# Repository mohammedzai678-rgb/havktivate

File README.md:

# Jeevan Voice Agent

A predictive voice companion for the **VitaWatch ESP32 hardware** (MAX30102 pulse/SpO₂, MAX30205 body
temperature, OLED; the scan flow uses MAX30102 and MAX30205 only). It learns the wearer's normal, forecasts what is coming, and **speaks first**
through a Bluetooth headset (ElevenLabs voice, Gemini wording) — e.g. *"Your heartbeat seems a little fast.
Are you feeling nervous?"* — then listens for the answer, guides breathing, and (only after a clear "yes")
prepares a caregiver message.

```
msrus/
├─ firmware/jeevancare_esp32/   ESP32 C/C++ firmware — identical to VitaWatch (same pins, same Wi‑Fi, same endpoint)
├─ server/                      Python (FastAPI): ESP32 link + ElevenLabs TTS + Gemini dialogue
└─ web/                         Vite + React + TypeScript: the single Voice Agent page
```

## Hardware (unchanged)
Same board, wiring and Wi‑Fi as before — see `firmware/jeevancare_esp32/config.h`.
The ESP32 sends live readings and receives scan commands directly from the laptop over Wi-Fi. Set LOCAL_BACKEND_BASE_URL in config.h to the laptop's current Wi-Fi IPv4 address. Keep the laptop and ESP32 on the same network; the server must be reachable on port 8001.

## Run it

**1. Server** (Python 3.10+)
```powershell
cd server
python -m venv .venv
.\.venv\Scripts\pip install -r requirements.txt
copy .env.example .env        # then fill in ELEVENLABS_API_KEY and GEMINI_API_KEY
.\.venv\Scripts\python -m uvicorn main:app --host 0.0.0.0 --port 8001 --reload
```
Optional: configure the Supabase URL and service-role key in server/.env to sync telemetry and saved readings to the cloud. Sensor selection and reading history use the local service and remain available when Supabase is temporarily unreachable; offline readings are stored in server/data/scan_readings.json.

**2. Web**
```powershell
cd web
npm install
npm run dev                   # http://localhost:5173
```

**3. Headset**: pair the Bluetooth headset in Windows and set it as the default **input and output**,
open the page in Chrome, press **Start Voice Agent** (this unlocks audio so the agent may speak first).

## How the prediction works (all on the laptop, nothing learned in the cloud)
- **Learned pattern** – a personal baseline per vital (saved in the browser), updated only from non‑abnormal readings.
- **Time‑to‑event** – 60 s linear trend → "reaches attention level in ~N s (confidence %)".
- **Risk score** – 0–100 that climbs as precursors build, with a +60 s projection.
- **Speak first** – when the forecast/learned drift says something is coming, the agent opens the conversation, says *why*, then listens.
- **Adapts** – "I'm fine" makes it ask a little less about that topic next time; "not well" makes it ask sooner.

Complete HR/SpO2/temperature scans are saved to Supabase vitawatch_readings when server credentials are configured, or to server/data/scan_readings.json otherwise. Raw ESP32 samples continue to be logged to server/data/vitals_log.csv.

*Assistive early‑warning only — not a medical device, no diagnosis.*

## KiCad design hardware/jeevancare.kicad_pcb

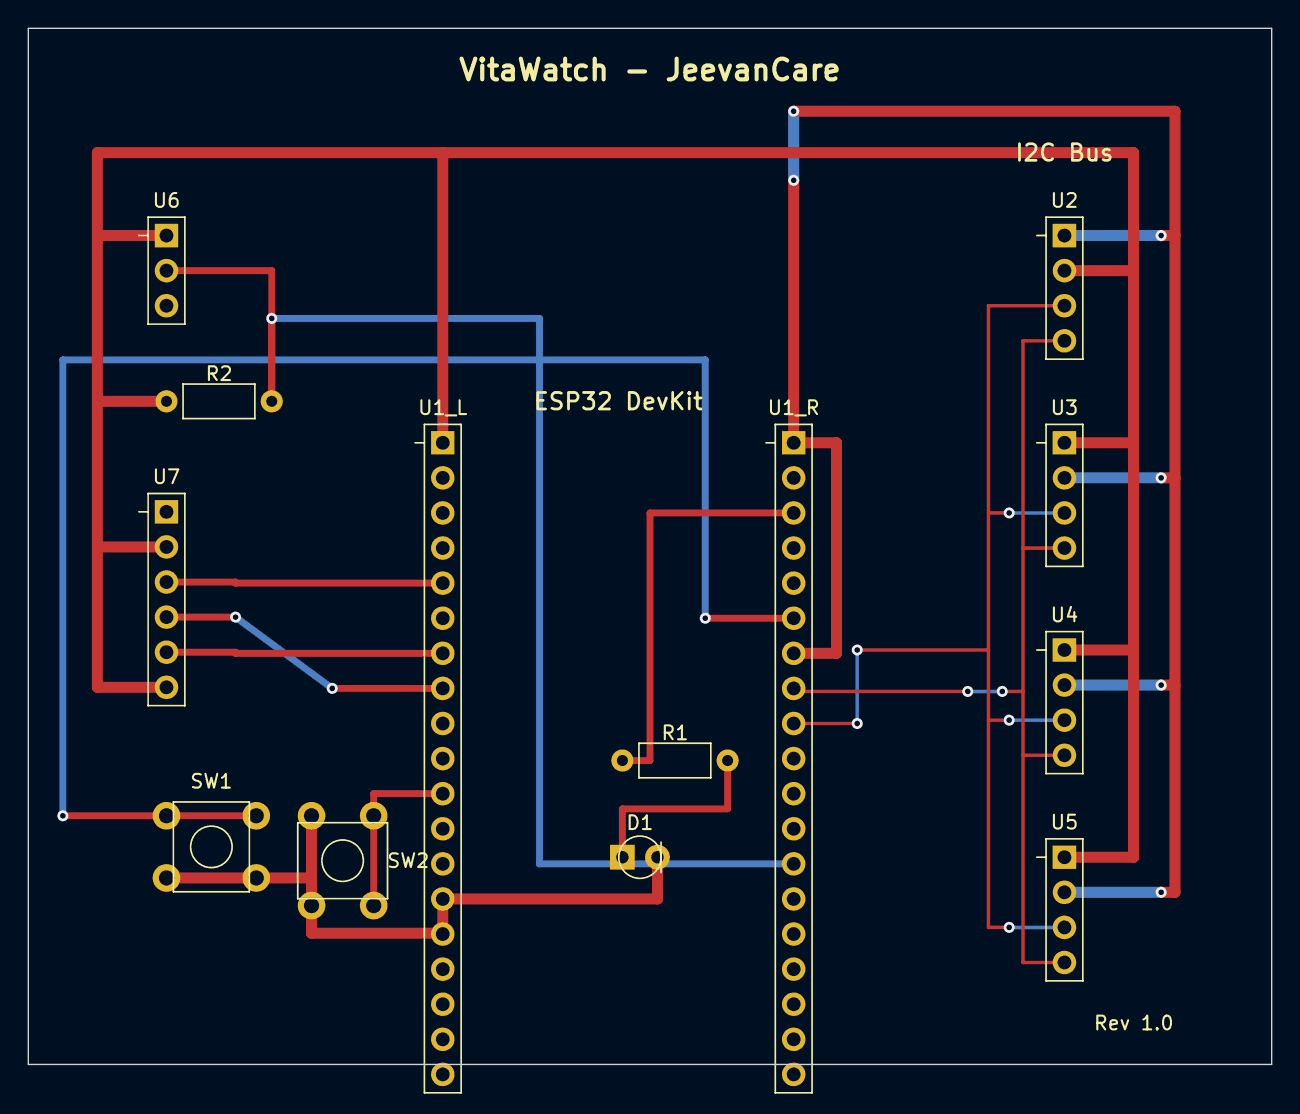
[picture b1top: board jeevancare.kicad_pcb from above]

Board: 2 copper layers, 90.0 x 75.0 mm, 13 parts (0 on the bottom side), 12 nets.

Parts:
D1: LED_Medicine; LED_D3.0mm
R1: 220R; R_Axial_DIN0207_L6.3mm_D2.5mm_P7.62mm_Horizontal
R2: 4.7k; R_Axial_DIN0207_L6.3mm_D2.5mm_P7.62mm_Horizontal
SW1: Medicine_ACK; SW_PUSH_6mm
SW2: Screen_Button; SW_PUSH_6mm
U1_L: ESP32_DevKit_Left; PinHeader_1x19_P2.54mm_Vertical
U1_R: ESP32_DevKit_Right; PinHeader_1x19_P2.54mm_Vertical
U2: SSD1306_OLED; PinHeader_1x04_P2.54mm_Vertical
U3: MAX30102; PinHeader_1x04_P2.54mm_Vertical
U4: MAX30205; PinHeader_1x04_P2.54mm_Vertical
U5: DS3231_RTC; PinHeader_1x04_P2.54mm_Vertical
U6: DHT11; PinHeader_1x03_P2.54mm_Vertical
U7: AD8232_ECG; PinHeader_1x06_P2.54mm_Vertical

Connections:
+3V3: R2.1, U1_L.1, U2.2, U3.1, U4.1, U5.1, U6.1, U7.2, U7.6
GND: D1.2, SW1.2, SW2.2, U1_L.14, U1_R.1, U1_R.7, U2.1, U3.2, U4.2, U5.2, U6.3, U7.1
GPIO4: R2.2, U1_R.13, U6.2
GPIO21: SW1.1, U1_R.6
GPIO22: R1.1, U1_R.3
GPIO27: SW2.1, U1_L.11
GPIO32: U1_L.7, U7.5
GPIO33: U1_L.8, U7.4
GPIO34: U1_L.5, U7.3
R1_LED: D1.1, R1.2
SCL: U1_R.9, U2.3, U3.3, U4.3, U5.3
SDA: U1_R.8, U2.4, U3.4, U4.4, U5.4

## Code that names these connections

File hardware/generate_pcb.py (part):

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    (2, "+3V3"),
    (3, "SDA"),
    (4, "SCL"),
    (5, "GPIO22"),
    (6, "GPIO21"),
    (7, "GPIO27"),
    (8, "GPIO4"),
    (9, "GPIO34"),
    (10, "GPIO33"),
    (11, "GPIO32"),
    (12, "R1_LED"),
]

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    segments.append(seg(25.5, 66.5, 21.5, 66.5, 0.8, 1))       # SW1 pin 2b
    segments.append(seg(21.5, 66.5, 15.0, 66.5, 0.8, 1))       # SW1 pin 2a

    # 5. GPIO22 (Net 5, 0.5mm): U1_R pin 3 (60.4, 40.08) -> R1 pin 1 (48, 58)
    segments.append(seg(60.4, 40.08, 50.0, 40.08, 0.5, 5))
    segments.append(seg(50.0, 40.08, 50.0, 58.0, 0.5, 5))
    segments.append(seg(50.0, 58.0, 48.0, 58.0, 0.5, 5))

    # 6. R1_LED (Net 12, 0.5mm): R1 pin 2 (55.62, 58) -> D1 pin 1 (48, 65)
    segments.append(seg(55.62, 58.0, 55.62, 61.5, 0.5, 12))
    segments.append(seg(55.62, 61.5, 48.0, 61.5, 0.5, 12))
    segments.append(seg(48.0, 61.5, 48.0, 65.0, 0.5, 12))

    # 7. GPIO21 (Net 6, 0.5mm): U1_R pin 6 (60.4, 47.70) -> SW1 pin 1 (15, 62)
    # Via right at (54, 47.70) to B.Cu immediately:
    segments.append(seg(60.4, 47.70, 54.0, 47.70, 0.5, 6))
    vias.append(via(54.0, 47.70, 6))
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    segments.append(seg(7.5, 62.0, 15.0, 62.0, 0.5, 6))        # SW1 pin 1a
    segments.append(seg(15.0, 62.0, 21.5, 62.0, 0.5, 6))       # SW1 pin 1b

    # 8. GPIO27 (Net 7, 0.5mm): U1_L pin 11 (35, 60.40) -> SW2 pin 1 (30, 62 & 30, 68.5)
    segments.append(seg(35.0, 60.40, 30.0, 60.40, 0.5, 7))
    segments.append(seg(30.0, 60.40, 30.0, 62.0, 0.5, 7))      # SW2 pin 1a
    segments.append(seg(30.0, 62.0, 30.0, 68.5, 0.5, 7))       # SW2 pin 1b

    # 9. GPIO4 (Net 8, 0.5mm): U1_R pin 13 (60.4, 65.48) -> DHT11 pin 2 (15, 22.54) & R2 pin 2 (22.62, 32)
    segments.append(seg(15.0, 22.54, 22.62, 22.54, 0.5, 8))
    segments.append(seg(22.62, 22.54, 22.62, 32.0, 0.5, 8))
    segments.append(seg(22.62, 32.0, 22.62, 26.0, 0.5, 8))
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    segments.append(seg(42.0, 26.0, 42.0, 65.48, 0.5, 8, layer="B.Cu"))
    segments.append(seg(42.0, 65.48, 60.4, 65.48, 0.5, 8, layer="B.Cu"))

    # 10. GPIO34 (Net 9, 0.5mm): U1_L pin 5 (35, 45.16) -> AD8232 OUTPUT U7 pin 3 (15, 45.08)
    segments.append(seg(35.0, 45.16, 20.0, 45.16, 0.5, 9))
    segments.append(seg(20.0, 45.16, 20.0, 45.08, 0.5, 9))
    segments.append(seg(20.0, 45.08, 15.0, 45.08, 0.5, 9))

    # 11. GPIO32 (Net 11, 0.5mm): U1_L pin 7 (35, 50.24) -> AD8232 LO+ U7 pin 5 (15, 50.16)
    segments.append(seg(35.0, 50.24, 20.0, 50.24, 0.5, 11))
    segments.append(seg(20.0, 50.24, 20.0, 50.16, 0.5, 11))
    segments.append(seg(20.0, 50.16, 15.0, 50.16, 0.5, 11))

    # 12. GPIO33 (Net 10, 0.5mm): U1_L pin 8 (35, 52.78) -> AD8232 LO- U7 pin 4 (15, 47.62)
    segments.append(seg(35.0, 52.78, 27.0, 52.78, 0.5, 10))
    vias.append(via(27.0, 52.78, 10))
    segments.append(seg(27.0, 52.78, 20.0, 47.62, 0.5, 10, layer="B.Cu"))
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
